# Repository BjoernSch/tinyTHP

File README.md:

tinyTHP
=======

RFM12B based TinyTX Transmitter with SI7021 and BMP180 on board

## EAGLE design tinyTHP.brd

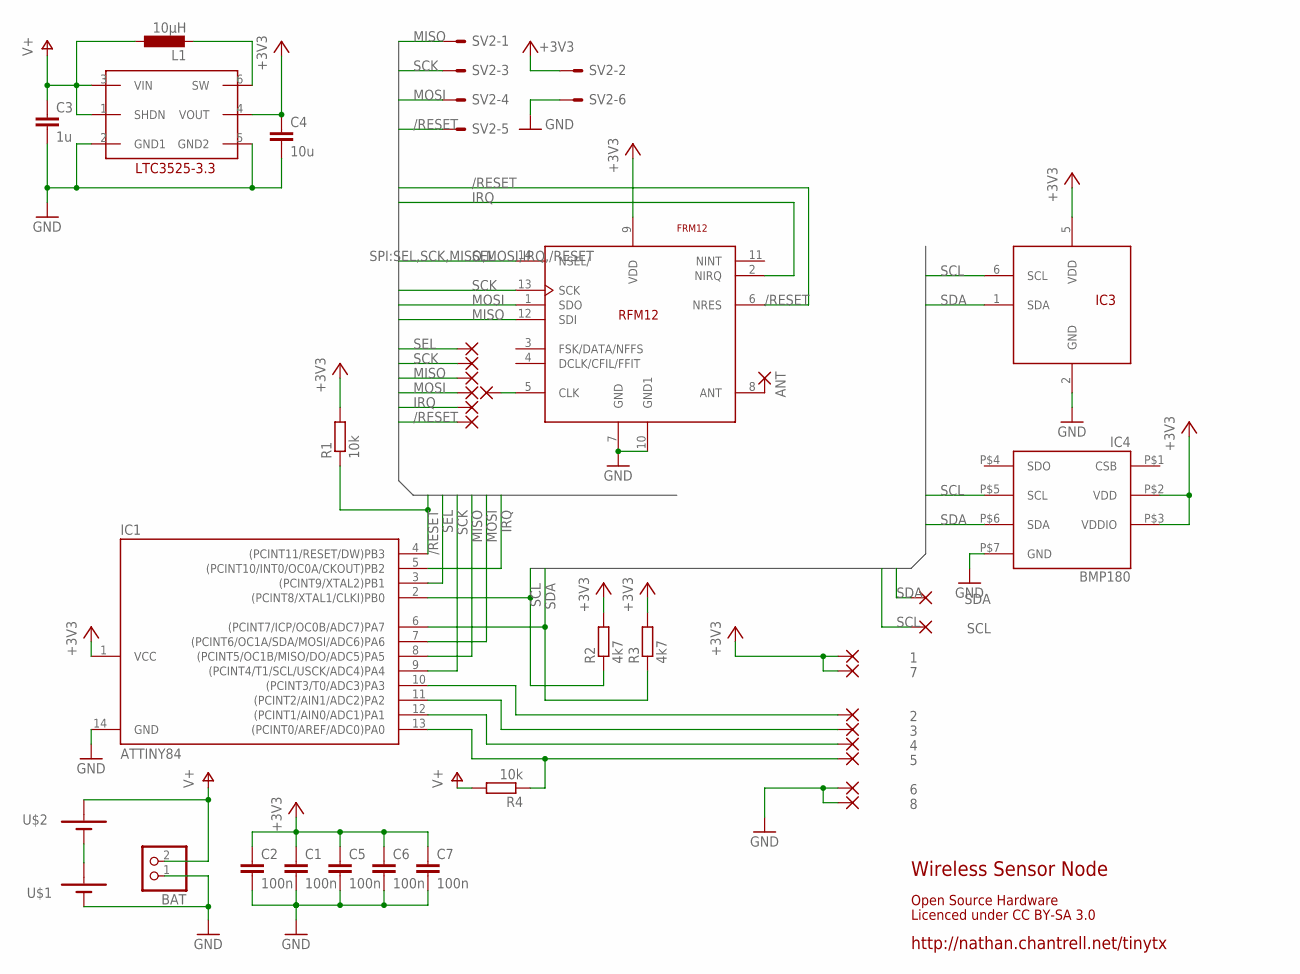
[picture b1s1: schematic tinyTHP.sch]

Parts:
1, 2, 3, 4, 5, 6, 7, 8: 1,6/0,9
/IRQ: 1,6/0,9
/RESET: 1,6/0,9
ANT: 1,6/0,8
BAT: PINHD-1X2; 1X02
C1, C2, C5, C6, C7: 100n; C0603
C3: 1u; C0603
C4: 10u; C0603
IC1: ATTINY84; SOIC14
IC2: IC2; SC70-6
IC3: SI7021; DFN-6
IC4: BMP180; LGA-7
L1: 10µH; L1616
MISO: 1,6/0,9
MOSI: 1,6/0,9
R1, R4: 10k; R0603
R2, R3: 4k7; R0603
RFMCLK: 1,6/0,9
SCK: 1,6/0,9
SCL: 1,6/0,9
SDA: 1,6/0,9
SEL: 1,6/0,9
SV2: ML6E; ML6
U$1, U$2: KEYSTONE-92-AA-BATTERY-HOLDER; KEYSTONE-92-AA-BATTERY
U$3: FRM12; RFM12

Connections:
+3V3: 1.1, 7.1, C1.1, C2.1, C4.1, C5.1, C6.1, C7.1, IC1.1 (VCC), IC2.4 (VOUT), IC3.5 (VDD), IC4.P$2 (VDD), IC4.P$3 (VDDIO), R1.2, R2.2, R3.2, SV2.2, U$3.9 (VDD)
/RESET: /RESET.1, IC1.4 ((PCINT11/RESET/DW)PB3), R1.1, SV2.5, U$3.6 (NRES)
ANT: ANT.1, U$3.8 (ANT)
GND: 6.1, 8.1, BAT.1, C1.2, C2.2, C3.2, C4.2, C5.2, C6.2, C7.2, IC1.14 (GND), IC2.2 (GND1), IC2.5 (GND2), IC3.2 (GND), IC4.P$7 (GND), SV2.6, U$1.GND (-), U$1.GND2 (-), U$3.7 (GND), U$3.10 (GND1)
IRQ: /IRQ.1, IC1.5 ((PCINT10/INT0/OC0A/CKOUT)PB2), U$3.2 (NIRQ)
MISO: IC1.8 ((PCINT5/OC1B/MISO/DO/ADC5)PA5), MISO.1, SV2.1, U$3.12 (SDI)
MOSI: IC1.7 ((PCINT6/OC1A/SDA/MOSI/ADC6)PA6), MOSI.1, SV2.4, U$3.1 (SDO)
unnamed: 2.1, IC1.10 ((PCINT3/T0/ADC3)PA3)
unnamed: 3.1, IC1.11 ((PCINT2/AIN1/ADC2)PA2)
unnamed: 4.1, IC1.12 ((PCINT1/AIN0/ADC1)PA1)
unnamed: 5.1, IC1.13 ((PCINT0/AREF/ADC0)PA0), R4.1
unnamed: U$1.VBATT (+), U$1.VBATT1 (+), U$2.GND (-), U$2.GND2 (-)
unnamed: RFMCLK.1, U$3.5 (CLK)
unnamed: IC2.6 (SW), L1.P$2 (2)
SCK: IC1.9 ((PCINT4/T1/SCL/USCK/ADC4)PA4), SCK.1, SV2.3, U$3.13 (SCK)
SCL: IC1.2 ((PCINT8/XTAL1/CLKI)PB0), IC3.6 (SCL), IC4.P$5 (SCL), R2.1, SCL.1
SDA: IC1.6 ((PCINT7/ICP/OC0B/ADC7)PA7), IC3.1 (SDA), IC4.P$6 (SDA), R3.1, SDA.1
SEL: IC1.3 ((PCINT9/XTAL2)PB1), SEL.1, U$3.14 (NSEL/)
V+: BAT.2, C3.1, IC2.1 (SHDN), IC2.3 (VIN), L1.P$1 (1), R4.2, U$2.VBATT (+), U$2.VBATT1 (+)

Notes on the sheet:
http://nathan.chantrell.net/tinytx
Wireless Sensor Node
Licenced under CC BY-SA 3.0
Open Source Hardware

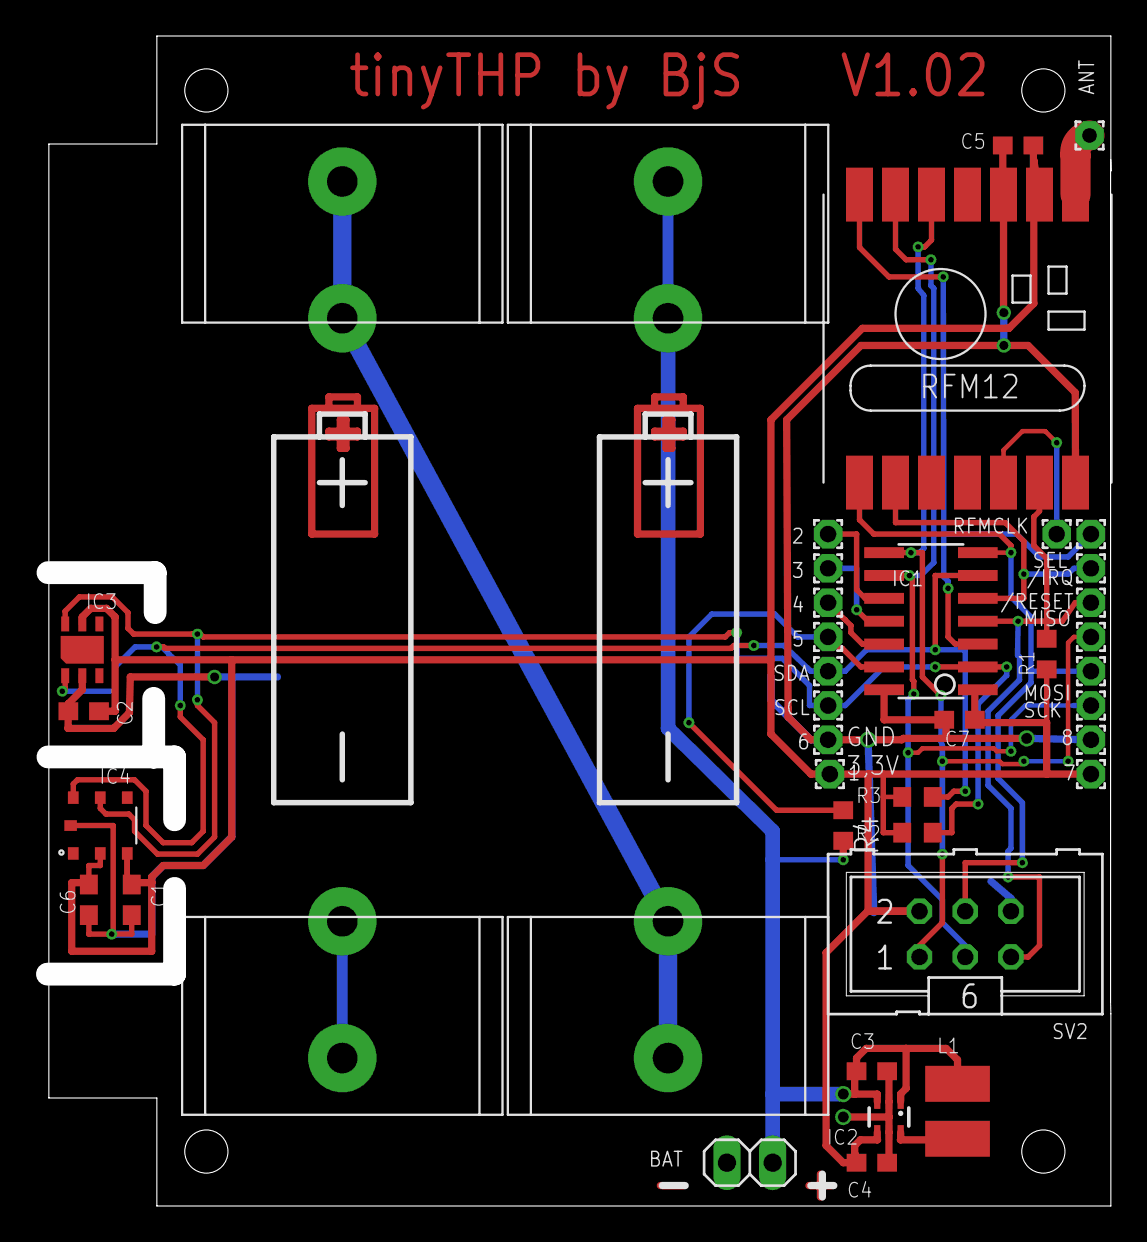
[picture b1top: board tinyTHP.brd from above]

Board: 2 copper layers, 58.4 x 63.7 mm, 39 parts (0 on the bottom side), 19 nets.

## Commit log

2015-01-18 Schaltplan und ayout hinzugefügt
